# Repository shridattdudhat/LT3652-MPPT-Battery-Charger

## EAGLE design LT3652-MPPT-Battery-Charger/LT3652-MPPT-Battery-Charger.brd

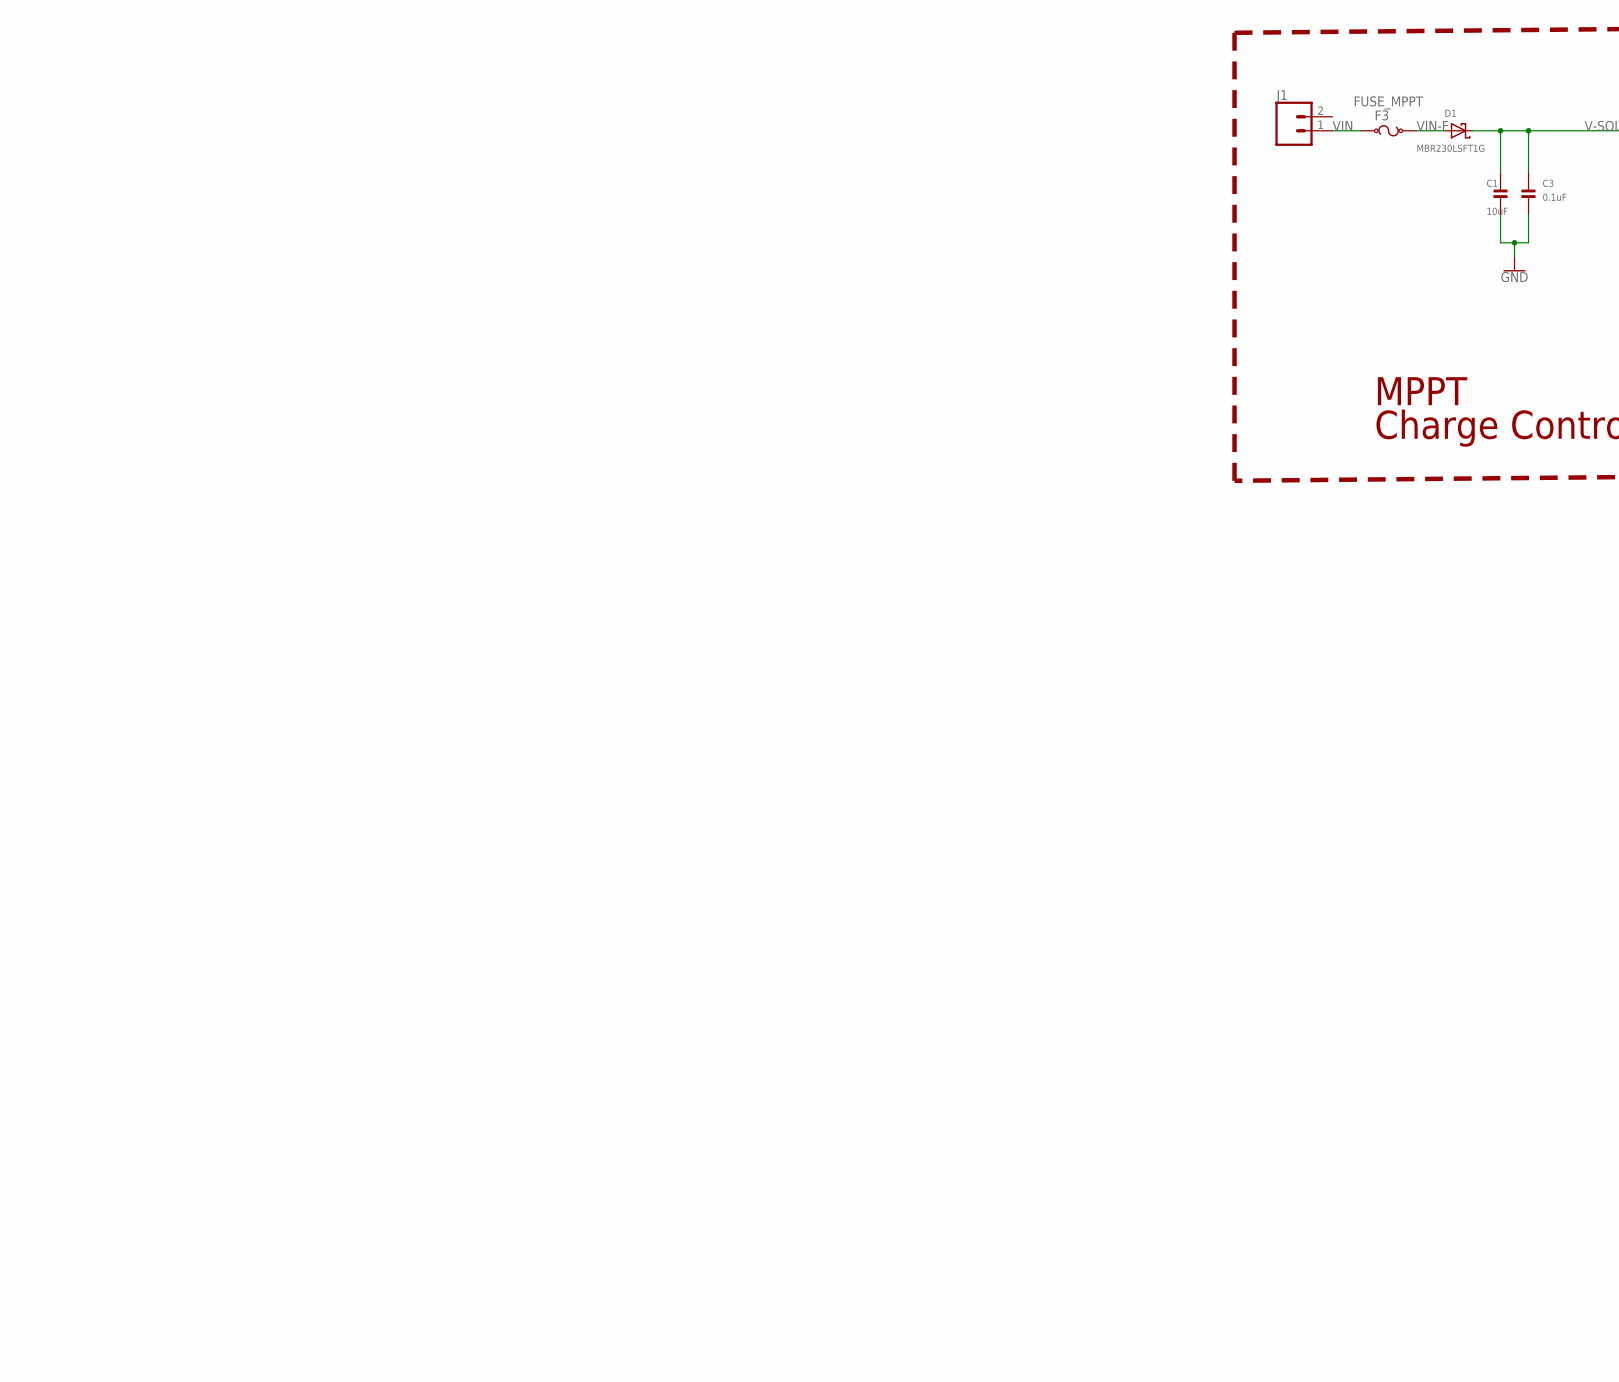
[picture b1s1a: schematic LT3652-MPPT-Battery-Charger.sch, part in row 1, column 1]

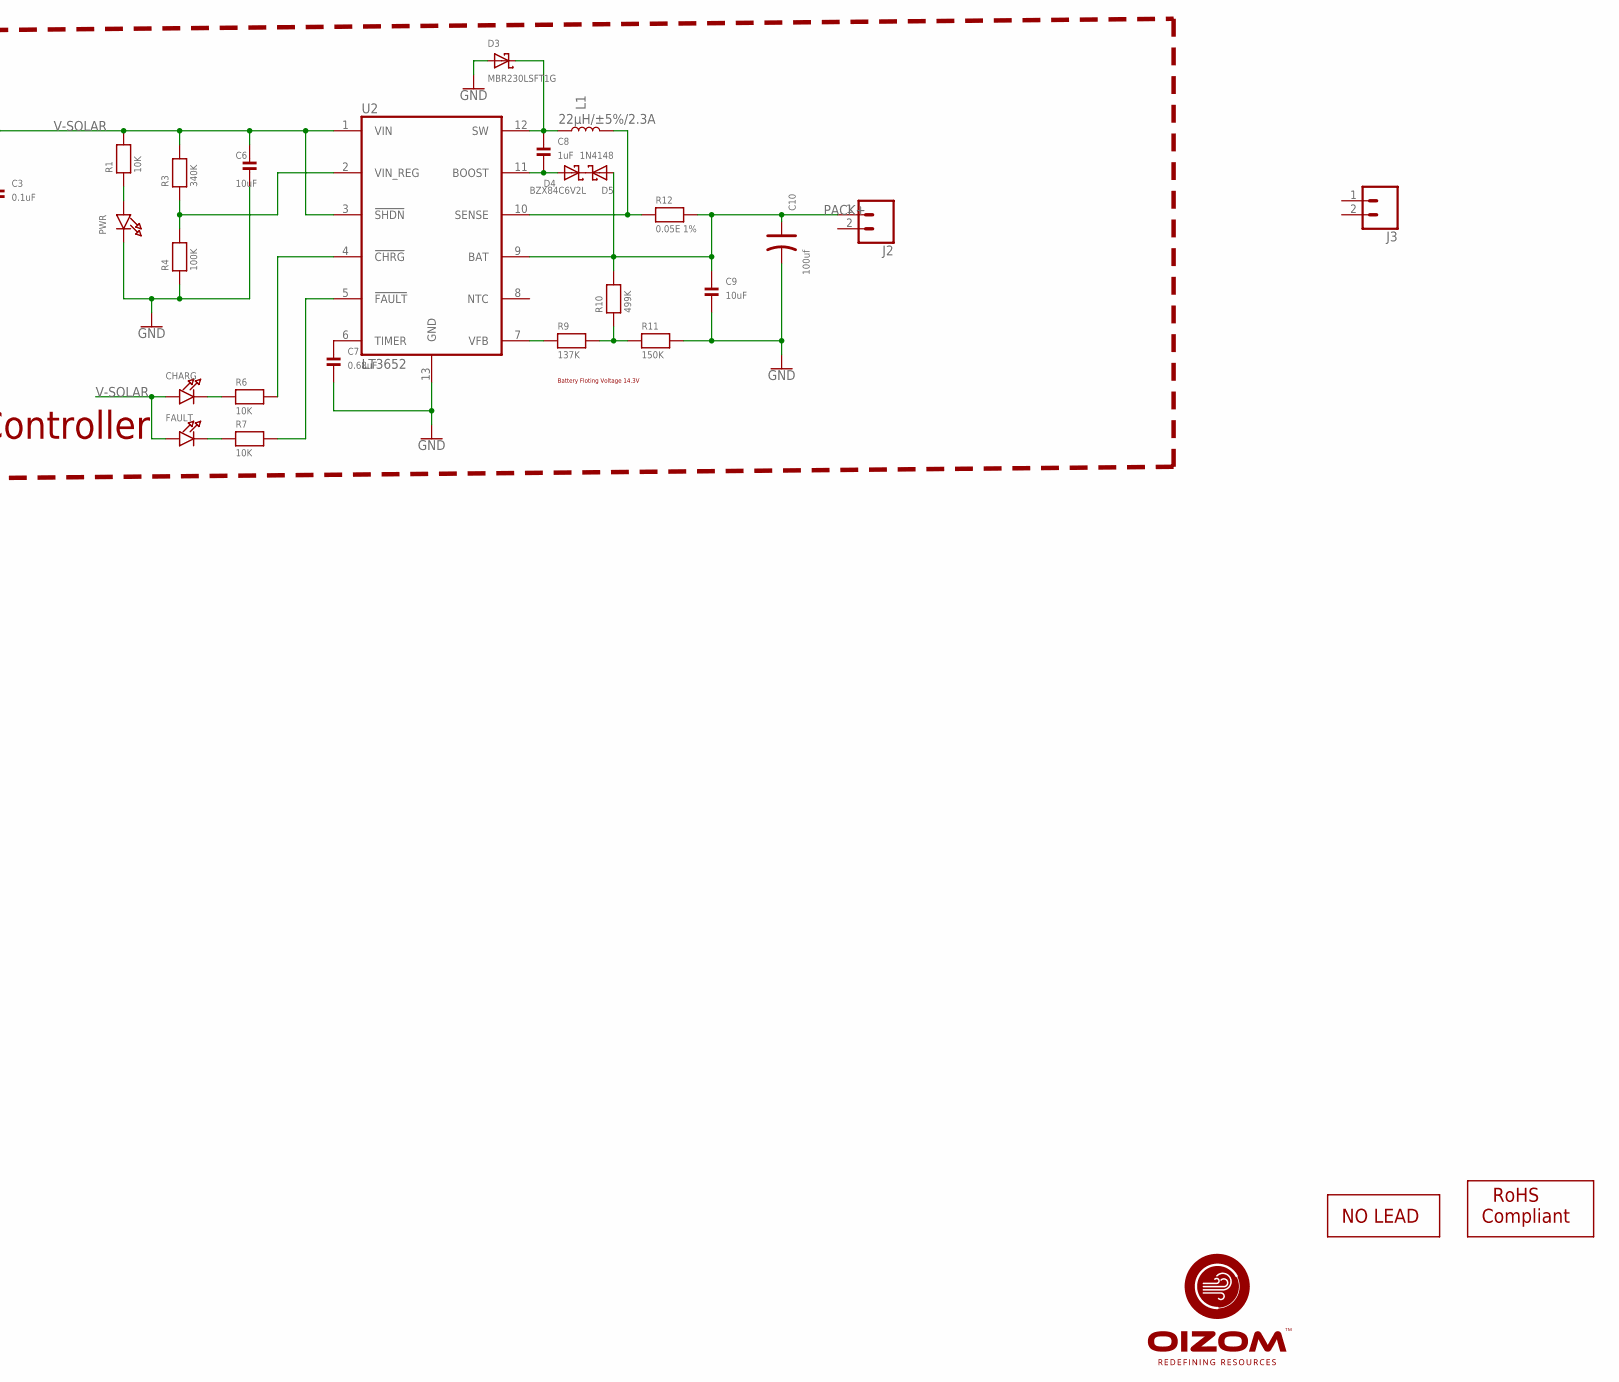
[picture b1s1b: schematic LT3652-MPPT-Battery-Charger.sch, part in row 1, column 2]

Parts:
C1, C6, C9: 10uF; 0805; MPN GRM21BR61E106KA73L
C3: 0.1uF; 0805; MPN 08055C104JAT2A
C7: 0.68uF; 0805; MPN CC0805KKX7R6BB684
C8: 1uF; 0805; MPN C0805C105K3RACTU
C10: 100uf; AVX-C; MPN TAJD107K016RNJ
CHARG: LED0603_NOOUTLINE; CHIPLED_0603_NOOUTLINE
D1, D3: MBR230LSFT1G; SOD-123; MPN MBR230LSFT1G
D4: BZX84C6V2L; SOT23-R; MPN BZX84C6V2LT1G
D5: 1N4148; SOD-323F; MPN 1N4148WS.
F3: FUSE_MPPT
FAULT: LED0603_NOOUTLINE; CHIPLED_0603_NOOUTLINE
J1, J2, J3: CONN_025MM; SCREWTERMINAL-5MM-2
L1: 22µH/±5%/2.3A; SRN6045; MPN SRN6045TA-100M
PWR: LED0603_NOOUTLINE; CHIPLED_0603_NOOUTLINE
R1, R6, R7: 10K; 0805; MPN RC0805FR-0710KL
R3: 340K; 0805; MPN ERJ6ENF3403V
R4: 100K; 0805; MPN MCWR08X1003FTL
R9: 137K; 0805; MPN ERJ6ENF1373V
R10: 499K; 0805; MPN ERJ6ENF5103V
R11: 150K; 0805; MPN ERJ6GEYJ154V
R12: 0.05E 1%; 0805; MPN ERJ6BWFR050V
U2: LT3652; MSOP12-MSE; MPN LT3652EMSE#PBF
U$1: NOPB_LOGO_SYM
U$2: ROHS_LOGO; ROHS_LOGO_SYM

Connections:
GND: C1.2, C3.2, C6.2, C7.2, C9.2, C10.-, D3.A, PWR.C, R4.1, R11.2, U2.13 (GND)
unnamed: PWR.A, R1.1
unnamed: R3.1, R4.2, U2.2 (VIN_REG)
unnamed: CHARG.C, R6.1
unnamed: R6.2, U2.4 (!CHRG!)
unnamed: R7.2, U2.5 (!FAULT!)
unnamed: C7.1, U2.6 (TIMER)
unnamed: C8.1, D3.C, L1.1, U2.12 (SW)
unnamed: L1.2, R12.1, U2.10 (SENSE)
unnamed: R9.1, U2.7 (VFB)
unnamed: R9.2, R10.1, R11.1
unnamed: D4.3 (C), D5.C
unnamed: C8.2, D4.1 (A), U2.11 (BOOST)
unnamed: FAULT.C, R7.1
PACK+: C9.1, C10.+, D5.A, J2.1, R10.2, R12.2, U2.9 (BAT)
V-SOLAR: C1.1, C3.1, C6.1, CHARG.A, D1.C, FAULT.A, R1.2, R3.2, U2.1 (VIN), U2.3 (!SHDN!)
VIN: F3.1, J1.1
VIN-F: D1.A, F3.2

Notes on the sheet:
D:/oizom-3.bmp
Battery Floting Voltage 14.3V
MPPT Charge Controller

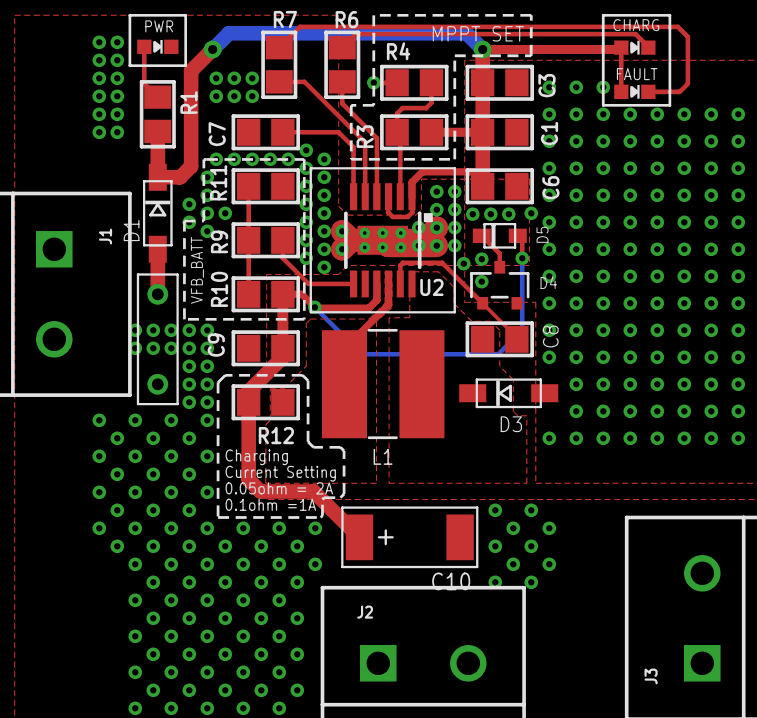
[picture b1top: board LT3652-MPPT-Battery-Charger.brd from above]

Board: 2 copper layers, 31 parts (1 on the bottom side), 18 nets.

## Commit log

2020-07-13 Set theme jekyll-theme-cayman
2020-07-14 Create Reference
2020-10-18 SCH Commit

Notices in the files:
parts and their libraries:
microbuilder: This work is placed in the public domain, and may be freely used for commercial and non-commercial work with the following conditions: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
SparkFun-Coils: Licensing: Creative Commons ShareAlike 4.0 International - https://creativecommons.org/licenses/by-sa/4.0
